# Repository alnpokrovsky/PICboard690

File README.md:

# PICboard690

Отладочная плата для pic16f690 в EagleCad

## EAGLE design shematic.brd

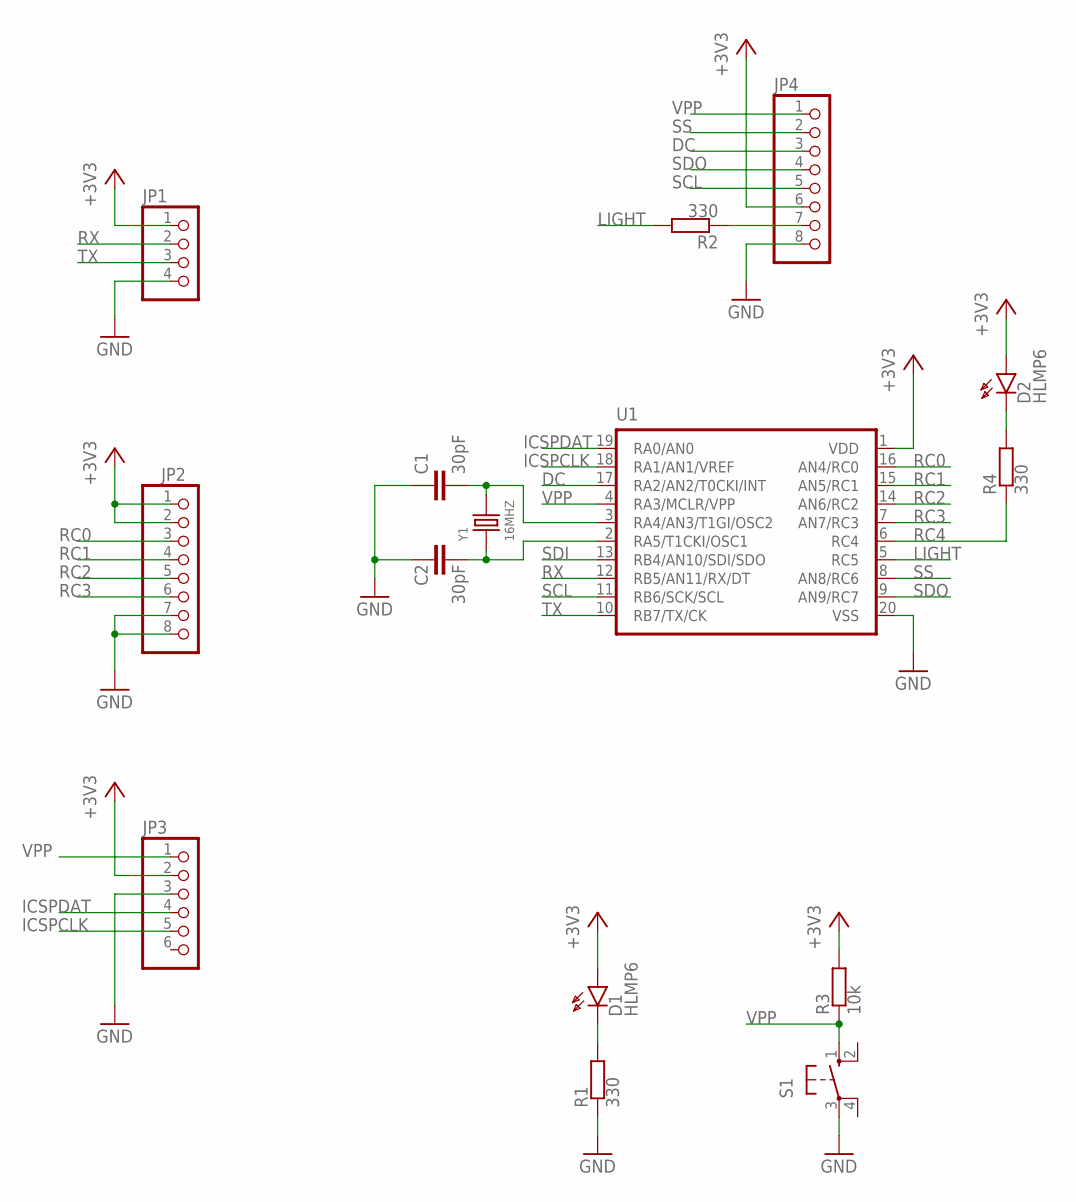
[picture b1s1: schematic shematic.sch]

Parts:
C1, C2: 30pF; C5B2.5
D1, D2: HLMP6
JP1: PINHD-1X4/90; 1X04/90
JP2, JP4: PINHD-1X8; 1X08
JP3: PINHD-1X6/90; 1X06/90
R1, R2, R4: 330; R0805
R3: 10k; 0204/7
S1: 10-XX; B3F-10XX
U1: PIC16F6XX; DIL20
Y1: 16MHZ; HC49US

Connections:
+3V3: D1.A, D2.A, JP1.1, JP2.1, JP2.2, JP3.2, JP4.6, R3.2, U1.1 (VDD)
DC: JP4.3, U1.17 (RA2/AN2/T0CKI/INT)
GND: C1.1, C2.1, JP1.4, JP2.7, JP2.8, JP3.3, JP4.8, R1.1, S1.3, U1.20 (VSS)
ICSPCLK: JP3.5, U1.18 (RA1/AN1/VREF)
ICSPDAT: JP3.4, U1.19 (RA0/AN0)
LIGHT: R2.2, U1.5 (RC5)
unnamed: C1.2, U1.3 (RA4/AN3/T1GI/OSC2), Y1.2
unnamed: C2.2, U1.2 (RA5/T1CKI/OSC1), Y1.1
unnamed: D1.K, R1.2
unnamed: D2.K, R4.2
unnamed: JP4.7, R2.1
RC0: JP2.3, U1.16 (AN4/RC0)
RC1: JP2.4, U1.15 (AN5/RC1)
RC2: JP2.5, U1.14 (AN6/RC2)
RC3: JP2.6, U1.7 (AN7/RC3)
RC4: R4.1, U1.6 (RC4)
RX: JP1.2, U1.12 (RB5/AN11/RX/DT)
SCL: JP4.5, U1.11 (RB6/SCK/SCL)
SDI: U1.13 (RB4/AN10/SDI/SDO)
SDO: JP4.4, U1.9 (AN9/RC7)
SS: JP4.2, U1.8 (AN8/RC6)
TX: JP1.3, U1.10 (RB7/TX/CK)
VPP: JP3.1, JP4.1, R3.1, S1.1 (S), U1.4 (RA3/MCLR/VPP)

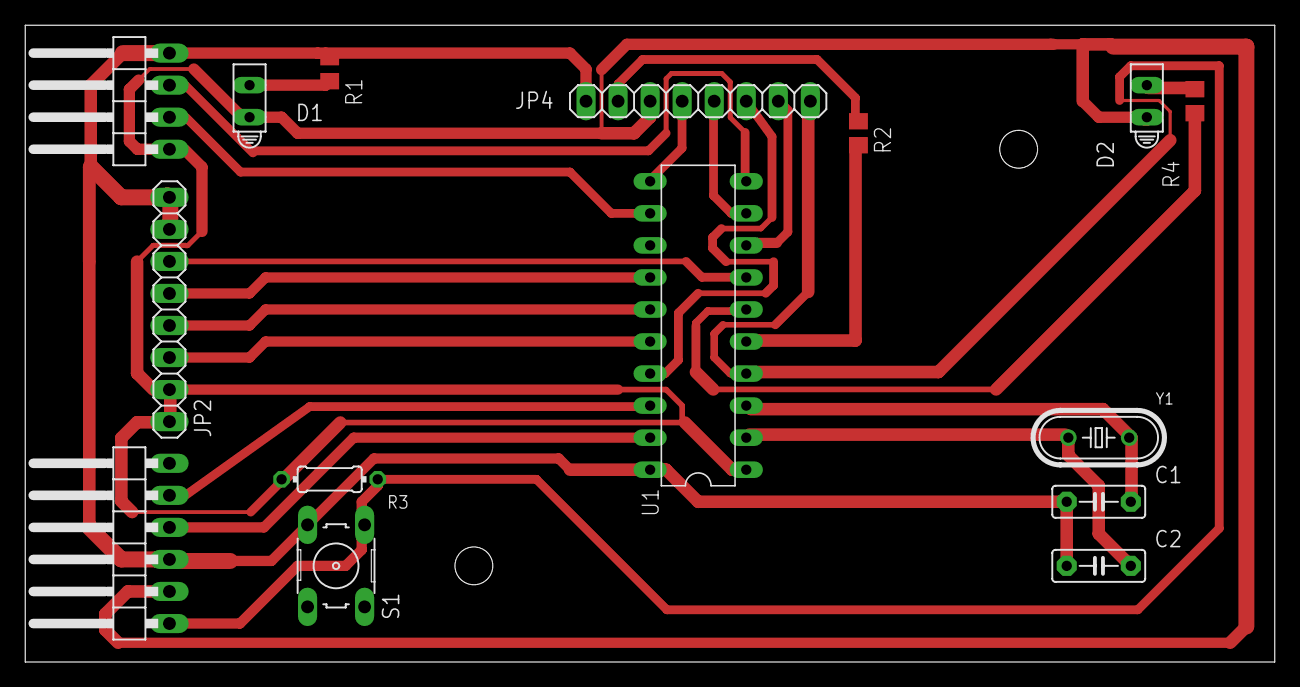
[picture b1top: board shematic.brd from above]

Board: 2 copper layers, 99.0 x 50.5 mm, 15 parts (0 on the bottom side), 22 nets.

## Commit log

2019-07-06 init
2019-07-16 set taller routes width
2019-07-16 fix some wires
2019-07-17 mounting holes
2019-07-17 fix warnings
